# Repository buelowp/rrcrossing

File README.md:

# In track IR sensor for realistic crossing signals
This is a HW project based on a RPi Pico which will monitor 4 track sensors to determine which way a train is going, and then operate flashers and gates for one crossing. This actually works really well so far. But it needs more testing.

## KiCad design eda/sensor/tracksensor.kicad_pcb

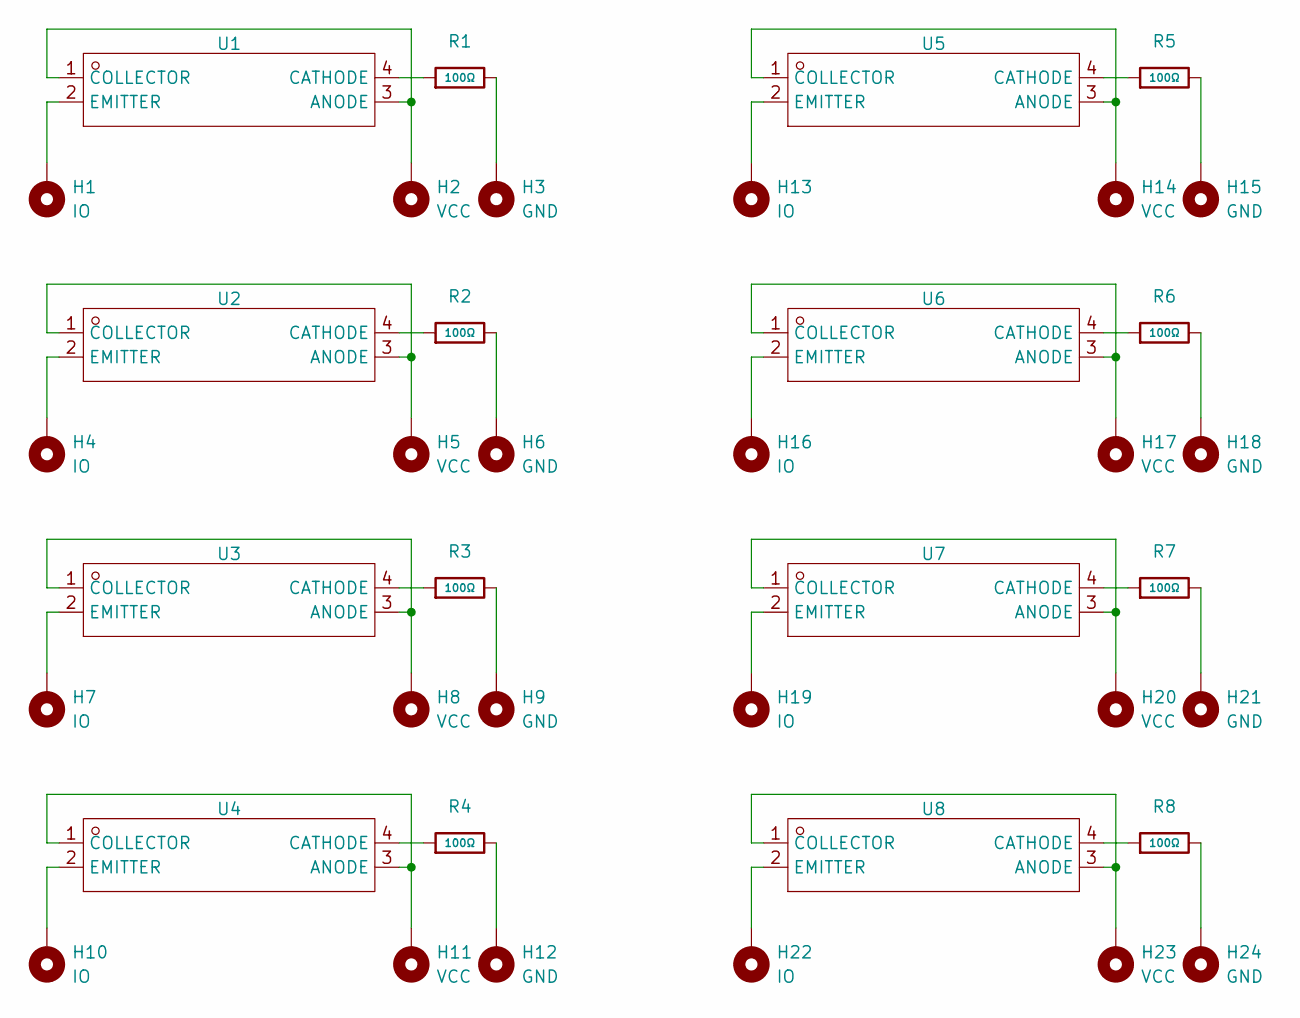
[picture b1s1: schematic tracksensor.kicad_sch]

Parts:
H1, H4, H7, H10, H13, H16, H19, H22: IO; TestPoint_Pad_1.5x1.5mm
H2, H5, H8, H11, H14, H17, H20, H23: VCC; TestPoint_Pad_1.5x1.5mm
H3, H6, H9, H12, H15, H18, H21, H24: GND; TestPoint_Pad_1.5x1.5mm
R1, R2, R3, R4, R5, R6, R7, R8: 100Ω; R_0402; Overload Voltage (Max) 50V; Tolerance ±1%; Part 0402WGF1000TCE; LCSC C25076
U1, U2, U3, U4, U5, U6, U7, U8: OPTO-SMD-4_ITR1204SR10A; Manufacturer Part ITR1204SR10A/TR(BY); LCSC Part Name 光电开关(ITR)

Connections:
unnamed: H3.1, R1.2
unnamed: H6.1, R2.2
unnamed: H9.1, R3.2
unnamed: H12.1, R4.2
unnamed: H15.1, R5.2
unnamed: H18.1, R6.2
unnamed: H21.1, R7.2
unnamed: H24.1, R8.2
unnamed: H2.1, U1.1 (COLLECTOR), U1.3 (ANODE)
unnamed: R1.1, U1.4 (CATHODE)
unnamed: H1.1, U1.2 (EMITTER)
unnamed: H5.1, U2.1 (COLLECTOR), U2.3 (ANODE)
unnamed: R2.1, U2.4 (CATHODE)
unnamed: H4.1, U2.2 (EMITTER)
unnamed: H8.1, U3.1 (COLLECTOR), U3.3 (ANODE)
unnamed: R3.1, U3.4 (CATHODE)
unnamed: H7.1, U3.2 (EMITTER)
unnamed: H11.1, U4.1 (COLLECTOR), U4.3 (ANODE)
unnamed: R4.1, U4.4 (CATHODE)
unnamed: H10.1, U4.2 (EMITTER)
unnamed: H14.1, U5.1 (COLLECTOR), U5.3 (ANODE)
unnamed: R5.1, U5.4 (CATHODE)
unnamed: H13.1, U5.2 (EMITTER)
unnamed: H17.1, U6.1 (COLLECTOR), U6.3 (ANODE)
unnamed: R6.1, U6.4 (CATHODE)
unnamed: H16.1, U6.2 (EMITTER)
unnamed: H20.1, U7.1 (COLLECTOR), U7.3 (ANODE)
unnamed: R7.1, U7.4 (CATHODE)
unnamed: H19.1, U7.2 (EMITTER)
unnamed: H23.1, U8.1 (COLLECTOR), U8.3 (ANODE)
unnamed: R8.1, U8.4 (CATHODE)
unnamed: H22.1, U8.2 (EMITTER)

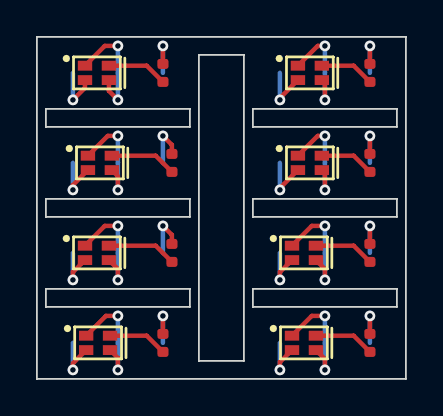
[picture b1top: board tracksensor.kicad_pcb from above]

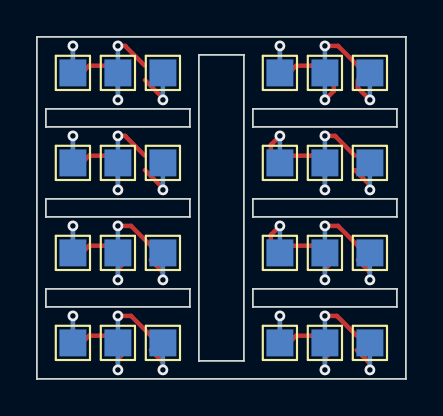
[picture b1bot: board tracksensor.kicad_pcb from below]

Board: 2 copper layers, 20.5 x 19.0 mm, 40 parts (24 on the bottom side), 32 nets.

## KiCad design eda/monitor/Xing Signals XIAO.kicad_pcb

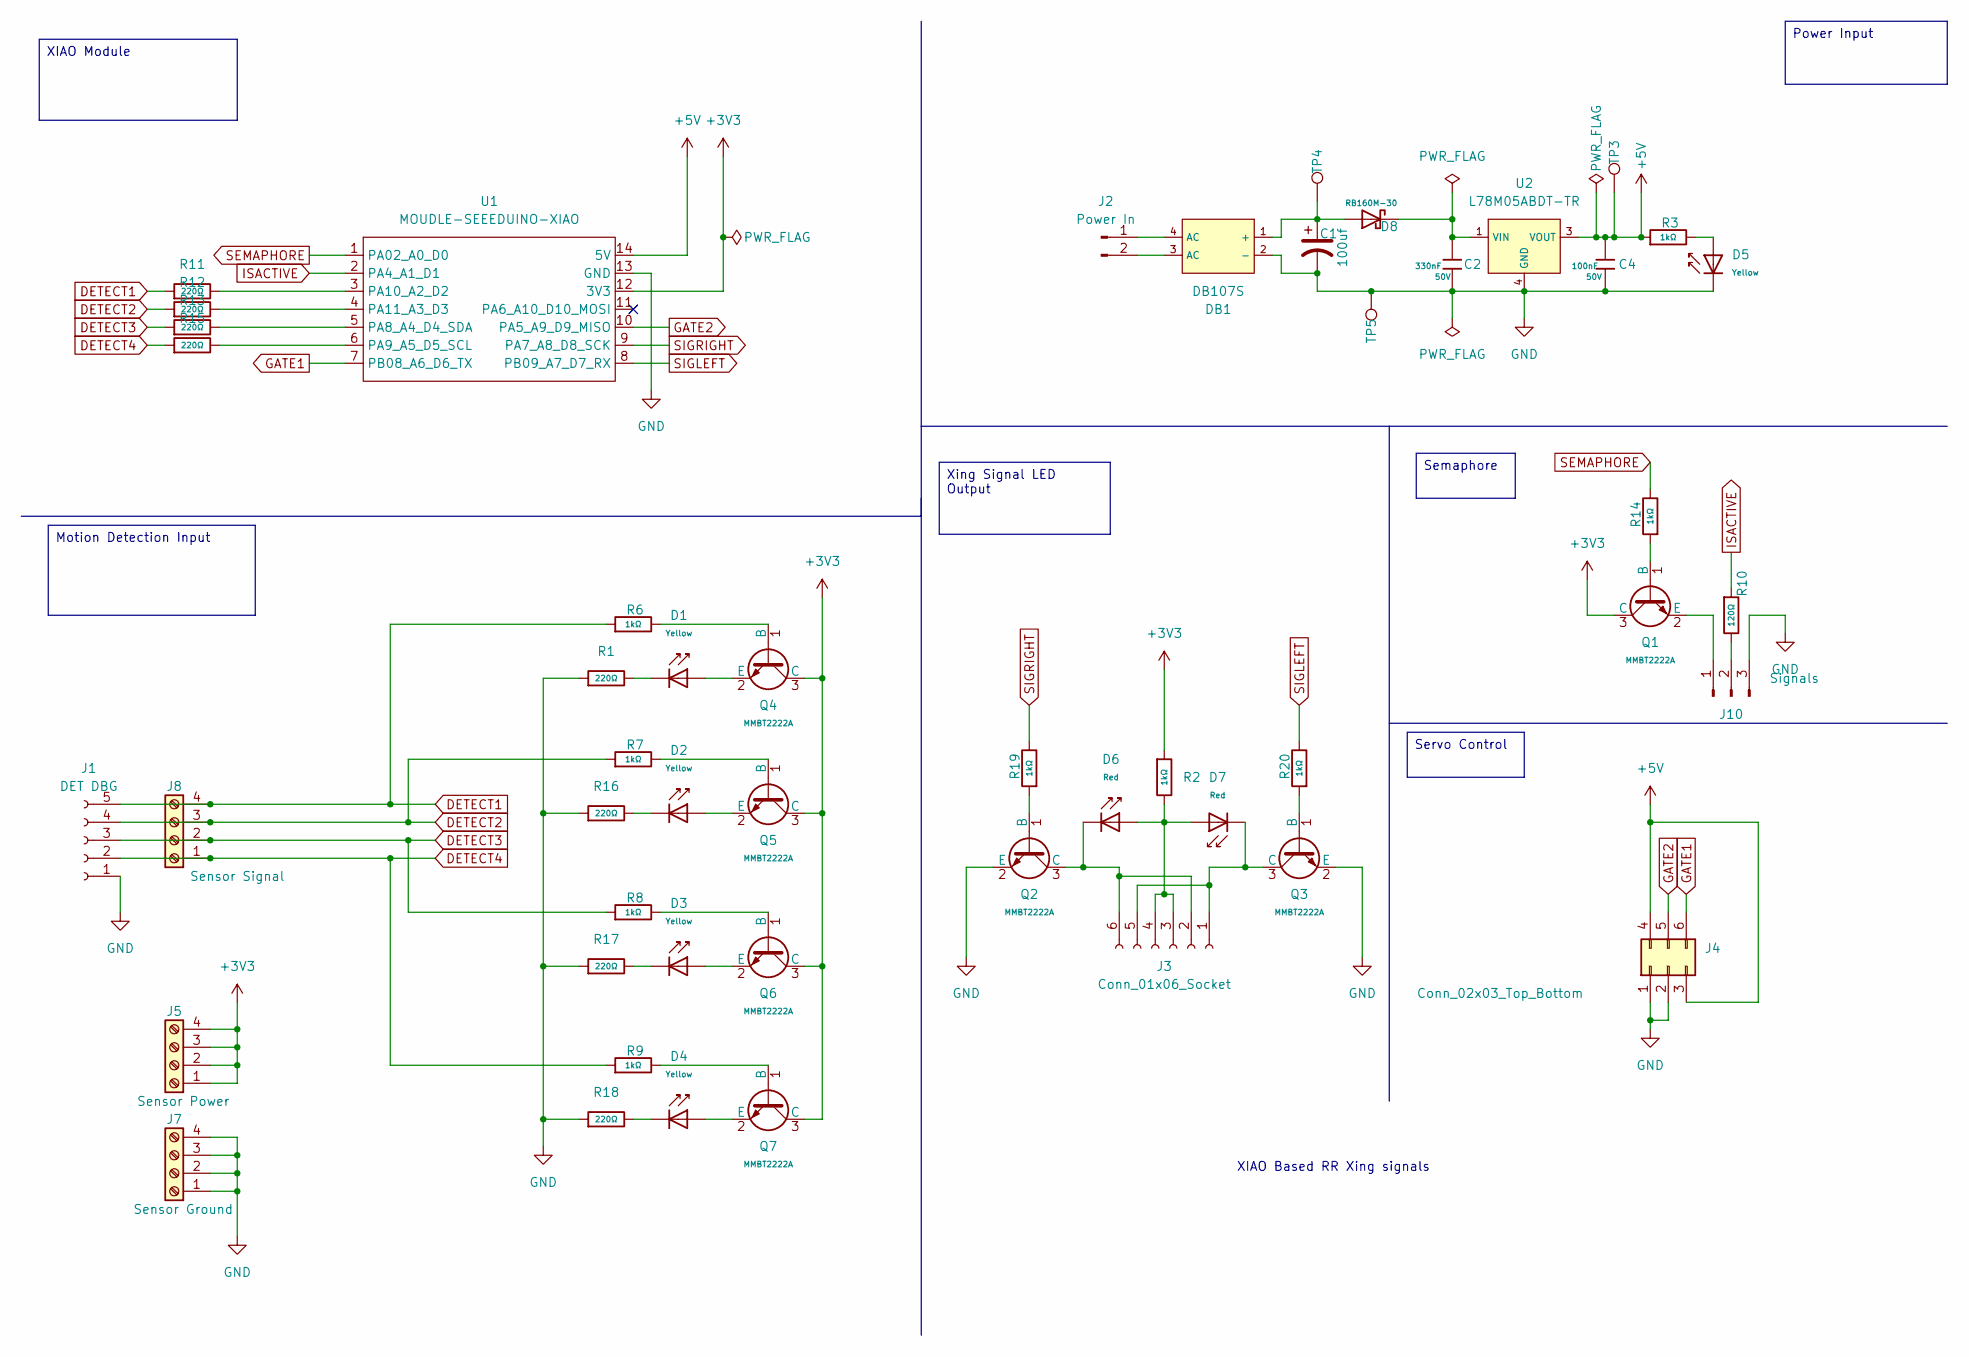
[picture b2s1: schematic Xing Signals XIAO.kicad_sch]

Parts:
C1: 100uf; CP_Radial_D5.0mm_P2.50mm
C2: 330nF; C_0805; Voltage Rated 50V; Tolerance ±10%; Part 0805B334K500NT; LCSC C1740
C4: 100nF; C_0603; Voltage Rated 50V; Tolerance ±10%; Part CC0603KRX7R9BB104; LCSC C14663
D1, D2, D3, D4, D5: Yellow; D_0603; Part 19-213/Y2C-CQ2R2L/3T(CY); LCSC C72038
D6, D7: Red; D_0603; Part KT-0603R; LCSC C2286
D8: RB160M-30; D_SOD-123; Forward Voltage (Vf@If) 480mV@1A; Reverse Voltage (Vr) 30V; Part RB160M-30; LCSC C7502715
DB1: DB107S; DBS_L8.2-W6.4-P5.10-LS10.0-BL; Reverse Voltage (Vr) 1kV; Forward Voltage (Vf@If) 1.1V@1A; Part DB107S; LCSC C5377
J1: DET DBG; PinHeader_1x05_P2.54mm_Vertical
J2: Power In; Molex_KK-396_A-41791-0002_1x02_P3.96mm_Vertical
J3: Conn_01x06_Socket; PinHeader_1x06_P2.54mm_Vertical
J4: Conn_02x03_Top_Bottom; PinHeader_2x03_P2.54mm_Vertical
J5: Sensor Power; PinHeader_1x04_P2.54mm_Vertical
J7: Sensor Ground; PinHeader_1x04_P2.54mm_Vertical
J8: Sensor Signal; PinHeader_1x04_P2.54mm_Vertical
J10: Signals; PinHeader_1x03_P2.54mm_Vertical
Q1, Q2, Q3, Q4, Q5, Q6, Q7: MMBT2222A; Q_SOT-23; Part MMBT2222A; LCSC C7420351
R1, R11, R12, R13, R15, R16, R17, R18: 220Ω; R_0402; Overload Voltage (Max) 50V; Tolerance ±1%; Part 0402WGF2200TCE; LCSC C25091
R2: 1kΩ; R_1206; Overload Voltage (Max) 200V; Tolerance ±1%; Part 1206W4F1001T5E; LCSC C4410
R3, R6, R7, R8, R9, R14, R19, R20: 1kΩ; R_0402; Overload Voltage (Max) 50V; Tolerance ±1%; Part 0402WGF1001TCE; LCSC C11702
R10: 120Ω; R_0402; Overload Voltage (Max) 50V; Tolerance ±1%; Part 0402WGF1200TCE; LCSC C25079
TP3, TP4, TP5: +5V; TestPoint_Pad_2.0x2.0mm
U1: MOUDLE-SEEEDUINO-XIAO; MOUDLE14P-2.54-21X17.8MM
U2: L78M05ABDT-TR; TO-252-2_L6.5-W6.1-P4.58-LS10.0-TL; Output Voltage 5V; Part L78M05ABDT-TR; LCSC C58069

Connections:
+3V3: J5.1, J5.2, J5.3, J5.4, Q1.3 (C), Q4.3 (C), Q5.3 (C), Q6.3 (C), Q7.3 (C), R2.1, U1.12 (3V3)
+5V: C4.1, J4.3, J4.4, R3.1, TP3.1, U1.14 (5V), U2.3 (VOUT)
DETECT1: J1.5, J8.4, R6.1, R11.1
DETECT2: J1.4, J8.3, R7.1, R12.1
DETECT3: J1.3, J8.2, R8.1, R13.1
DETECT4: J1.2, J8.1, R9.1, R15.1
GATE1: J4.6, U1.7 (PB08_A6_D6_TX)
GATE2: J4.5, U1.10 (PA5_A9_D9_MISO)
GND: C1.2, C2.2, C4.2, D5.1, DB1.2 (-), J1.1, J4.1, J4.2, J7.1, J7.2, J7.3, J7.4, J10.3, Q2.2 (E), Q3.2 (E), R1.1, R16.1, R17.1, R18.1, TP5.1, U1.13 (GND), U2.4 (GND); also elsewhere on the board
ISACTIVE: R10.1, U1.2 (PA4_A1_D1)
unnamed: D1.1, R1.2
unnamed: D2.1, R16.2
unnamed: D3.1, R17.2
unnamed: D4.1, R18.2
unnamed: D5.2, R3.2
unnamed: C1.1, D8.2, DB1.1 (+), TP4.1
unnamed: DB1.4 (AC), J2.1
unnamed: DB1.3 (AC), J2.2
unnamed: D7.1, J3.1, J3.5, Q3.3 (C)
unnamed: D6.1, J3.2, J3.6, Q2.3 (C)
unnamed: D6.2, D7.2, J3.3, J3.4, R2.2
unnamed: J10.1, Q1.2 (E)
unnamed: J10.2, R10.2
unnamed: Q1.1 (B), R14.1
unnamed: Q2.1 (B), R19.1
unnamed: Q3.1 (B), R20.1
unnamed: Q4.1 (B), R6.2
unnamed: D1.2, Q4.2 (E)
unnamed: Q5.1 (B), R7.2
unnamed: D2.2, Q5.2 (E)
unnamed: Q6.1 (B), R8.2
unnamed: D3.2, Q6.2 (E)
unnamed: Q7.1 (B), R9.2
unnamed: D4.2, Q7.2 (E)
unnamed: R13.2, U1.5 (PA8_A4_D4_SDA)
unnamed: R15.2, U1.6 (PA9_A5_D5_SCL)
unnamed: R11.2, U1.3 (PA10_A2_D2)
unnamed: R12.2, U1.4 (PA11_A3_D3)
unnamed: C2.1, D8.1, U2.1 (VIN)
SEMAPHORE: R14.2, U1.1 (PA02_A0_D0)
SIGLEFT: R20.2, U1.8 (PB09_A7_D7_RX)
SIGRIGHT: R19.2, U1.9 (PA7_A8_D8_SCK)

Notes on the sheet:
XIAO Based RR Xing signals
Xing Signal LED Output
Motion Detection Input
Servo Control
XIAO Module
Semaphore
Power Input

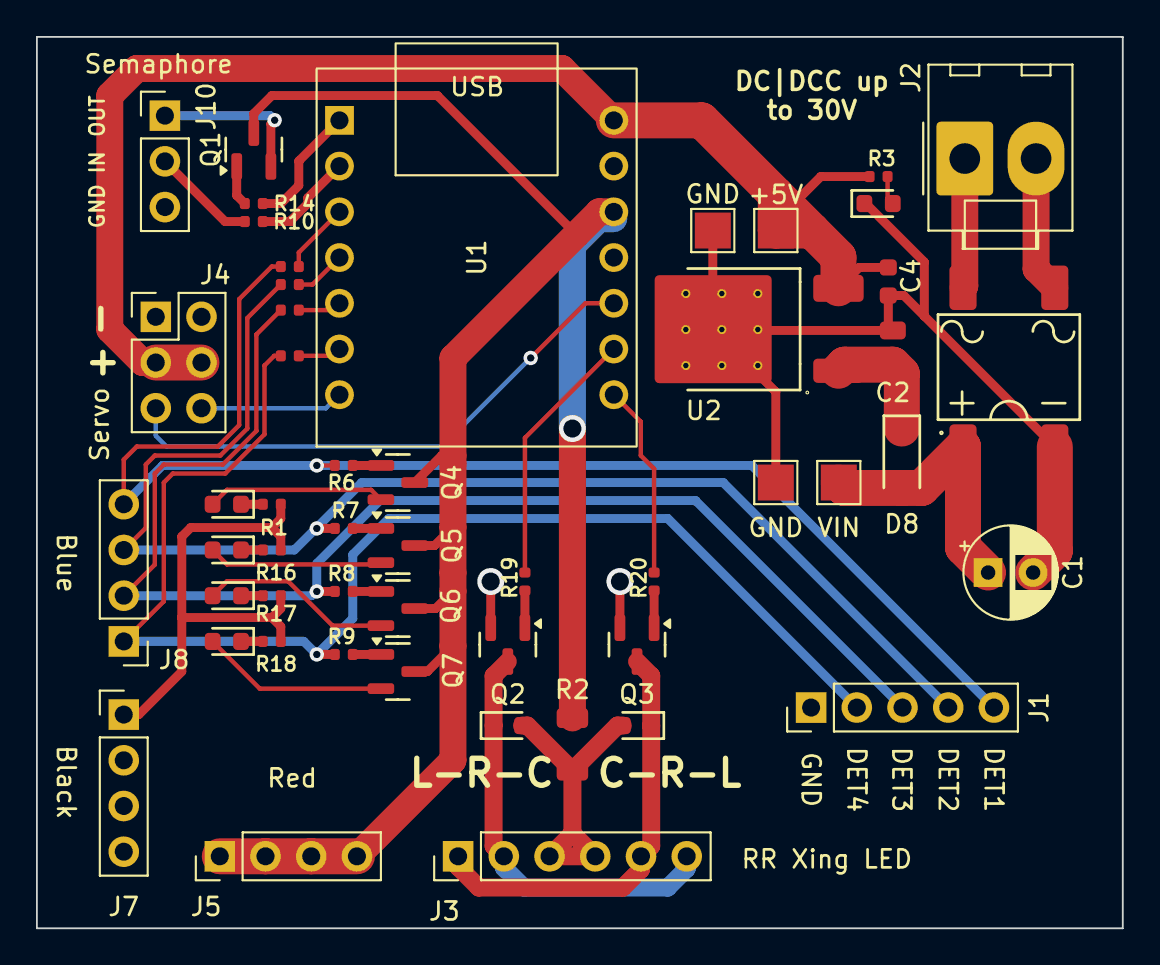
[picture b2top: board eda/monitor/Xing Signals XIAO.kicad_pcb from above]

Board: 2 copper layers, 60.3 x 49.5 mm, 51 parts (0 on the bottom side), 42 nets.

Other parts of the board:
TP1: GND; TestPoint_Pad_2.0x2.0mm

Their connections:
GND: TP1.1; also elsewhere on the board

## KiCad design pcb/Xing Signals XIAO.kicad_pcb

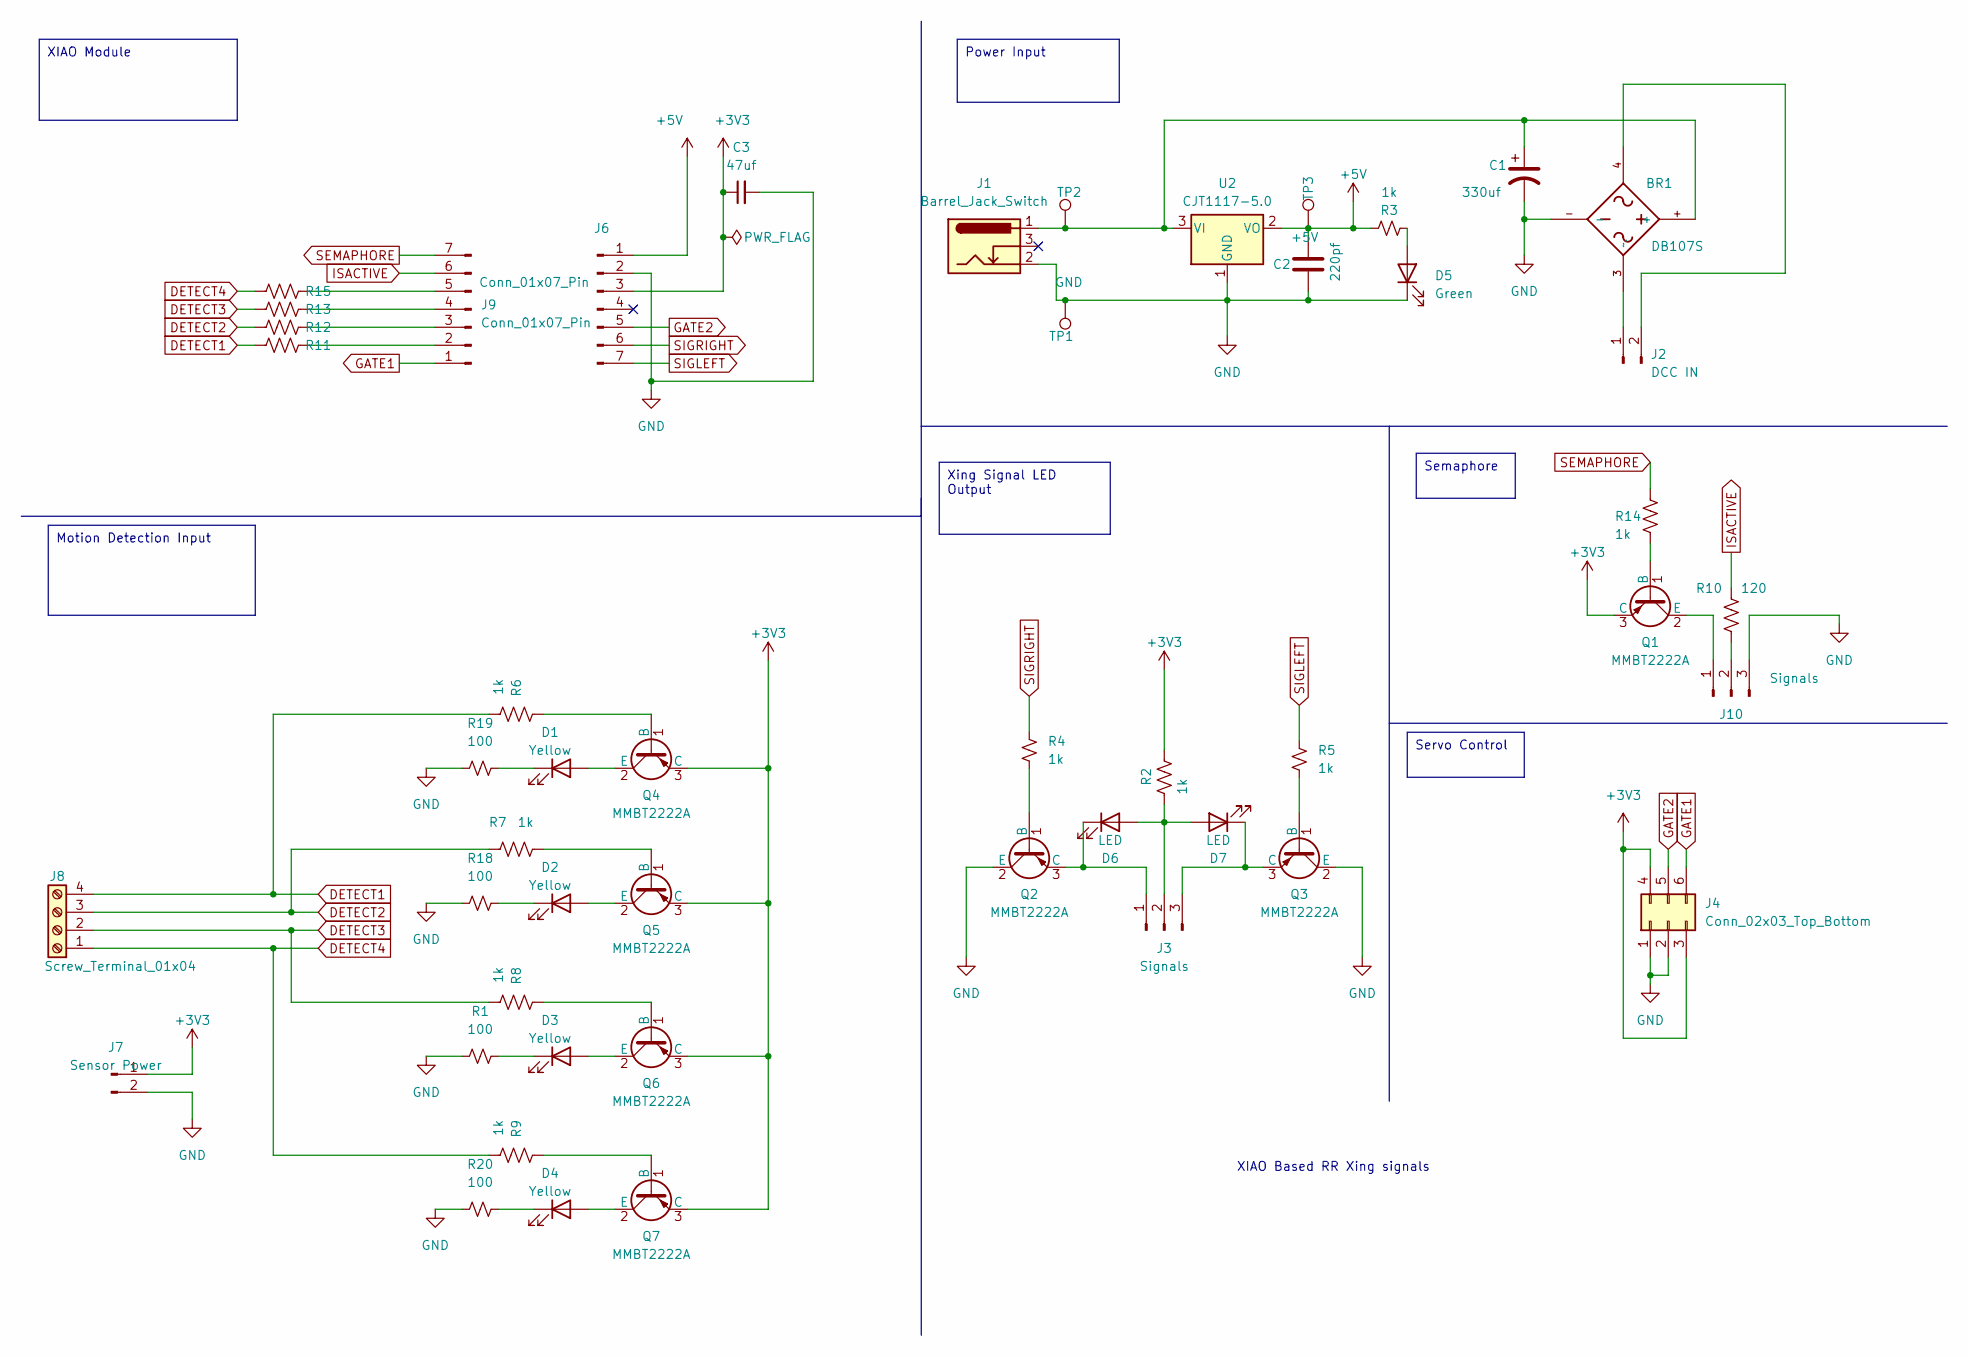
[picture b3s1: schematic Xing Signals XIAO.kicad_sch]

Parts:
BR1: DB107S; DIOB_DB107S; LCSC C5377
C1: 330uf; CP_Radial_D8.0mm_P3.80mm
C2: 220pf; C_0603_1608Metric; LCSC C1603
C3: 47uf; C_0805_2012Metric; LCSC C16780
D1, D2, D3, D4: Yellow; LED_0603_1608Metric; LCSC C72038
D5: Green; LED_0805_2012Metric; LCSC C2297
D6, D7: LED; LED_0603_1608Metric; LCSC C2286
J1: Barrel_Jack_Switch; BarrelJack_Horizontal
J2: DCC IN; Molex_KK-396_A-41791-0002_1x02_P3.96mm_Vertical
J3, J10: Signals; PinHeader_1x03_P2.54mm_Vertical
J4: Conn_02x03_Top_Bottom; PinHeader_2x03_P2.54mm_Vertical
J6, J9: Conn_01x07_Pin; PinHeader_1x07_P2.54mm_Vertical
J7: Sensor Power; PinHeader_1x02_P2.54mm_Vertical
J8: Screw_Terminal_01x04; PinHeader_1x04_P2.54mm_Vertical
Q1, Q2, Q3, Q4, Q5, Q6, Q7: MMBT2222A; SOT-23; LCSC C8512
R1, R18, R19, R20: 100; R_0402_1005Metric; LCSC C25076
R2: 1k; R_1206_3216Metric; LCSC C4410
R3, R4, R5, R6, R7, R8, R9, R14: 1k; R_0402_1005Metric; LCSC C105637
R10, R11, R12, R13, R15: 120; R_0402_1005Metric; LCSC C25079
TP1: GND; TestPoint_Pad_2.0x2.0mm
TP2: VIN; TestPoint_Pad_2.0x2.0mm
TP3: +5V; TestPoint_Pad_2.0x2.0mm
U2: CJT1117-5.0; SOT-223; LCSC C89273

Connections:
+3V3: C3.1, J4.3, J4.4, J6.3, J7.1, Q1.3 (C), Q4.3 (C), Q5.3 (C), Q6.3 (C), Q7.3 (C), R2.1
+5V: C2.1, J6.1, R3.1, TP3.1, U2.2 (VO)
DETECT1: J8.4, R6.2, R11.1
DETECT2: J8.3, R7.1, R12.1
DETECT3: J8.2, R8.2, R13.1
DETECT4: J8.1, R9.2, R15.1
GATE1: J4.6, J9.1
GATE2: J4.5, J6.5
GND: BR1.-, C1.2, C2.2, C3.2, D5.1 (K), J1.2, J4.1, J4.2, J6.2, J7.2, J10.3, Q2.2 (E), Q3.2 (E), R1.1, R18.1, R19.1, R20.1, TP1.1, U2.1 (GND)
ISACTIVE: J9.6, R10.1
unnamed: BR1.3 (~.), J2.1
unnamed: D1.2 (A), Q4.2 (E)
unnamed: D1.1 (K), R19.2
unnamed: D2.2 (A), Q5.2 (E)
unnamed: D2.1 (K), R18.2
unnamed: D3.2 (A), Q6.2 (E)
unnamed: D3.1 (K), R1.2
unnamed: D4.2 (A), Q7.2 (E)
unnamed: D4.1 (K), R20.2
unnamed: D5.2 (A), R3.2
unnamed: D6.2 (A), D7.2 (A), J3.2, R2.2
unnamed: D6.1 (K), J3.1, Q2.3 (C)
unnamed: D7.1 (K), J3.3, Q3.3 (C)
unnamed: BR1.4, J2.2
unnamed: J9.2, R11.2
unnamed: J9.3, R12.2
unnamed: J9.4, R13.2
unnamed: J9.5, R15.2
unnamed: J10.1, Q1.2 (E)
unnamed: J10.2, R10.2
unnamed: Q1.1 (B), R14.2
unnamed: Q2.1 (B), R4.2
unnamed: Q3.1 (B), R5.2
unnamed: Q4.1 (B), R6.1
unnamed: Q5.1 (B), R7.2
unnamed: Q6.1 (B), R8.1
unnamed: Q7.1 (B), R9.1
unnamed: BR1.+, C1.1, J1.1, TP2.1, U2.3 (VI)
SEMAPHORE: J9.7, R14.1
SIGLEFT: J6.7, R5.1
SIGRIGHT: J6.6, R4.1

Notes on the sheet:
Xing Signal LED Output
Motion Detection Input
Servo Control
XIAO Module
Semaphore
Power Input
XIAO Based RR Xing signals

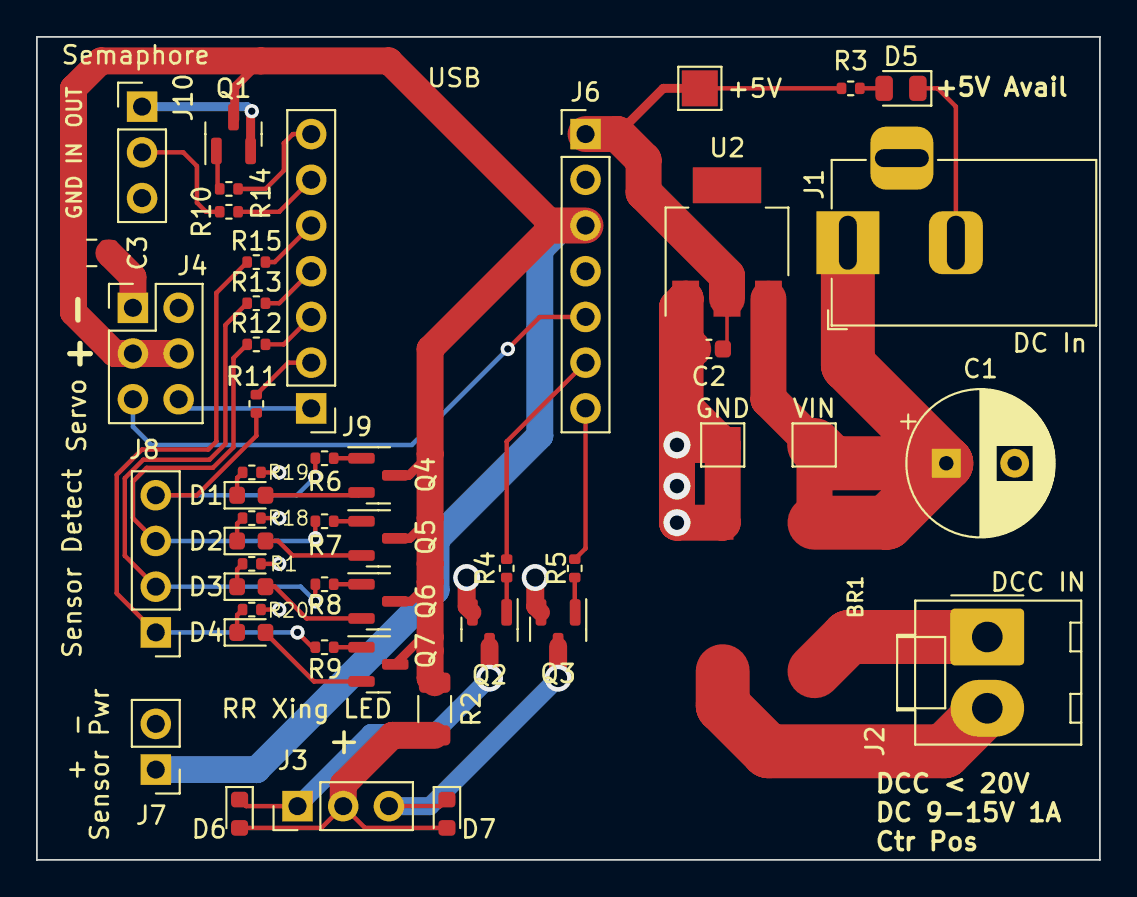
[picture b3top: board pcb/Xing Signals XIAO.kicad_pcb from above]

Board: 2 copper layers, 59.1 x 45.7 mm, 49 parts (0 on the bottom side), 41 nets.

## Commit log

2024-01-23 Initial commit
    * Doesn't work exactly right, but it's making progress
2024-01-24 Fixes
    * Add LED control
    * Fixup of state machine a bit
2024-01-27 Fix and debug changes
    * Fixed a bug with the sibling handling
    * Updated and fixed some printf calls
2024-01-27 Add the PCB work
2024-02-06 Version 1.1 of the PCB
2024-02-07 Fixes to Version 1.1
    * Trace fixups
    * Components moved to better fit
    * Move the sensor screw terminals next to each other
    * Cleaned up the transistor layout for the sensor LED indicators
    * Servo pins are now 2x3
2024-02-08 More fixes, ordered V1.1
    * Added C3 to buffer the Servo current draw
    * More fixes for traces
    * Fixed TP2 to be VIN, not +12V
2024-02-08 Version 1.2
    * Fixed a clearance issue between J3 and C2
    * Moved D6 and D7 a bit closer to J3
2025-02-27 Updating this and will make it public.
2025-02-27 Adding the track sensor in KiCad
